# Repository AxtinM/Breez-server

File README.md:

# Breez

### Resumé Technique :

1. VueJs
2. Websocket
3. NodeJs
4. Mqtt
5. ESP8266 Using WIFI Connection

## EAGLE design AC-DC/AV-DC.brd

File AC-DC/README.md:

# Convertisseur AC - > DC

## Power Supply PCB

## Power Supply Schematic

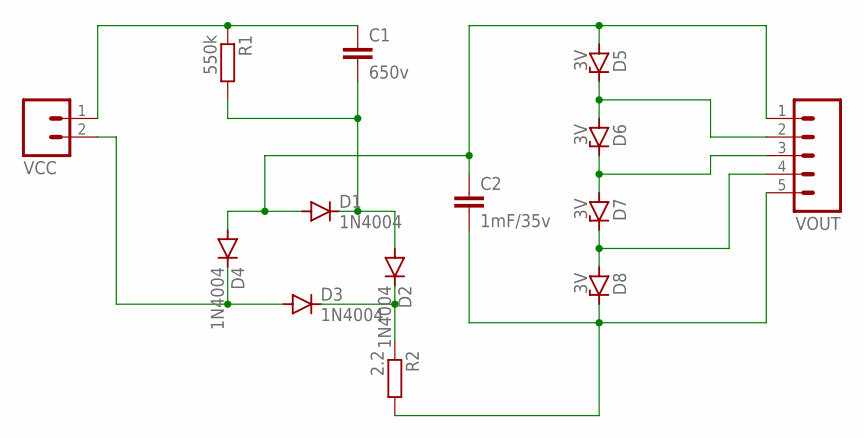
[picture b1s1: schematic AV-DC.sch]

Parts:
C1: 650v; C5B3
C2: 1mF/35v; C2.5-2
D1, D2, D3, D4: 1N4004; DO41-10
D5, D6, D7, D8: 3V; DO41Z10
R1: 550k; 0207/10
R2: 2.2; 0207/10
VCC: M02; 02P
VOUT: M05; 05P

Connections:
unnamed: C1.1, R1.1, VCC.1
unnamed: C1.2, D1.C, D2.A, R1.2
unnamed: C2.1, D1.A, D4.A, D5.A, VOUT.1
unnamed: D2.C, D3.C, R2.1
unnamed: D3.A, D4.C, VCC.2
unnamed: D5.C, D6.A, VOUT.2
unnamed: D6.C, D7.A, VOUT.3
unnamed: D7.C, D8.A, VOUT.4
unnamed: C2.2, D8.C, R2.2, VOUT.5

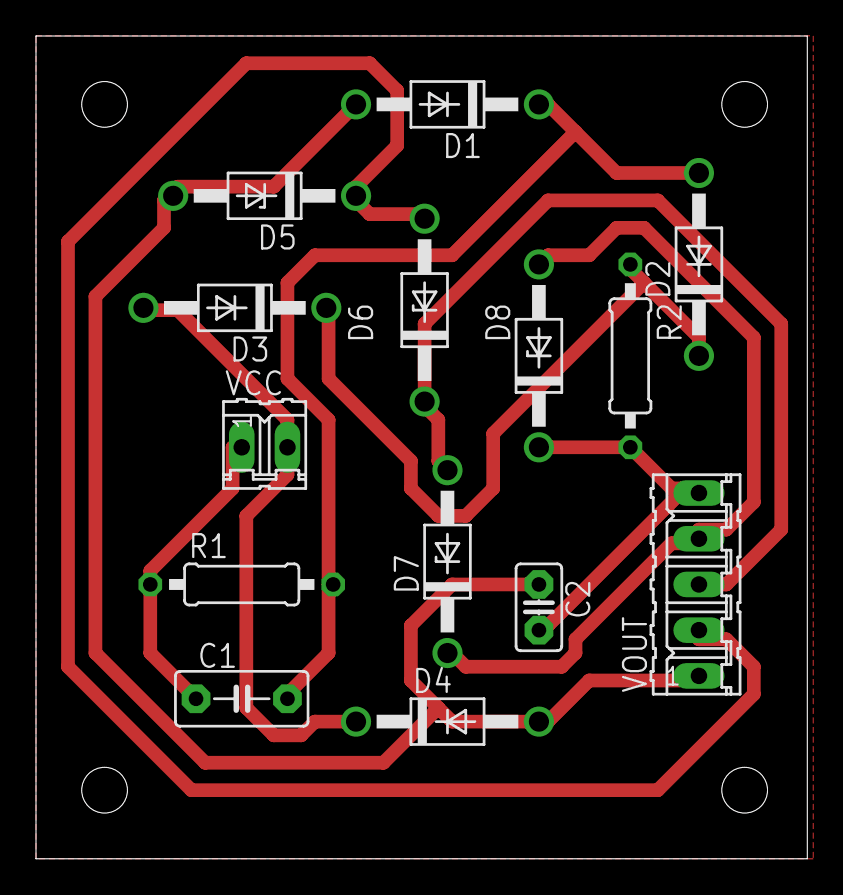
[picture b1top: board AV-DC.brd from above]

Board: 2 copper layers, 42.9 x 45.7 mm, 14 parts (0 on the bottom side), 9 nets.

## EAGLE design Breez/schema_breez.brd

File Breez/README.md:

# Conception du circuit imprimé pour Breez

## Breez PCB

## Breez Schematic

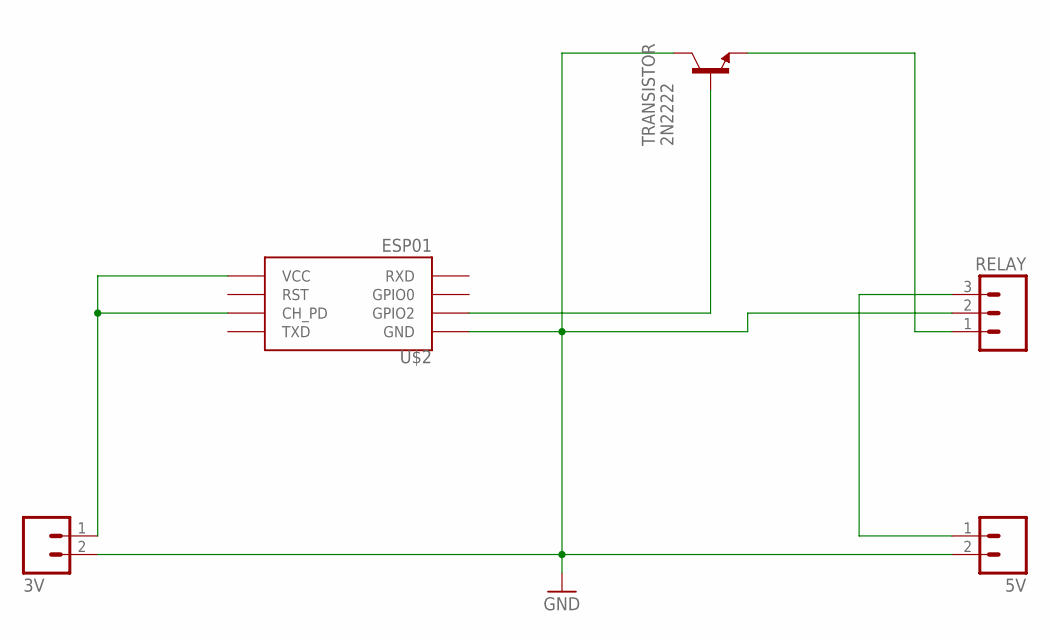
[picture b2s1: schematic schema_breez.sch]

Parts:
3V, 5V: M02; 02P
RELAY: M03; 03P
TRANSISTOR: 2N2222; TO18
U$2: ESP01

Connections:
GND: 3V.2, 5V.2, RELAY.2, TRANSISTOR.3 (C), U$2.GND
unnamed: RELAY.1, TRANSISTOR.1 (E)
unnamed: TRANSISTOR.2 (B), U$2.GPIO2
unnamed: 5V.1, RELAY.3
unnamed: 3V.1, U$2.CH_PD, U$2.VCC

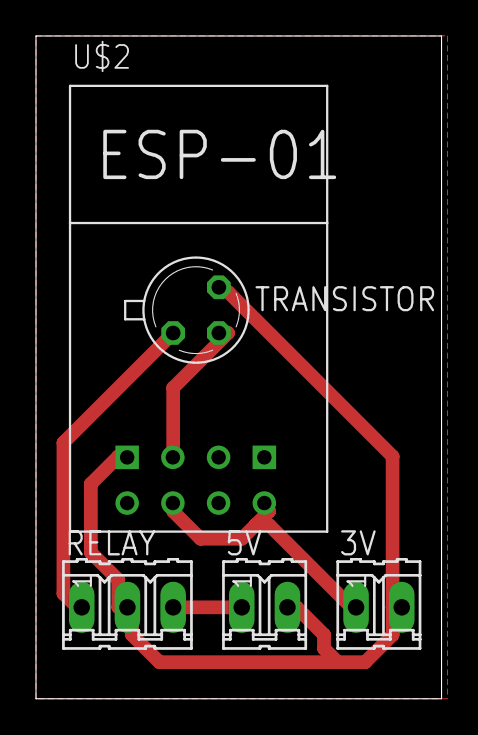
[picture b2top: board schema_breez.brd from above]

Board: 2 copper layers, 22.5 x 36.8 mm, 5 parts (0 on the bottom side), 5 nets.

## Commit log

2021-11-12 new file: README.md
2021-11-12 new file: mqtt_publisher.py new file: mqtt_subscriber.py
2021-11-14 added express layout and mqtt broker
2021-11-14 removed unnecessary files and updated README
2021-11-15 cleaning files and adding new api
2021-11-15 added Vue.js and updated README
2021-11-20 Update README.md
    delete codesandbox
2021-11-20 Update README.md
    delete messages
2021-11-20 added electronics code and established connection with server
2021-11-20 added README for electronics
2021-11-20 changed README
2021-11-21 added WebSocket between front and back
2021-11-23 added database models
2022-01-19 added pcb design files for breez
2022-01-19 added pcb design for AC to DC power supply
2022-01-19 added README for Breez & power Supply
2022-02-07 update mqtt with server and fixed errors
2022-02-21 backend CRUD and auth add
2022-02-26 adjusting ESP8266 code and communication with backend
2022-03-16 ready product
2022-04-04 added captive portal
2022-04-10 time controller, delete controller, user model, device model update
2022-07-19 new gitignore
